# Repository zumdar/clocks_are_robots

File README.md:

# clocks_are_robots
## ECE3872 musical robot team 5B 

Tinkercad Simulation of Arduino and circuity: <br>
https://www.tinkercad.com/things/kZ8lBtSx1vj-copy-of-ece3872-time-zeeper/editel?sharecode=Mxh5uRSaNloz5li4VxAIo-LYPFh9B_5_VCMgjHP5ZlA

**Arduino Pinouts**

A0 - Audio in <br>
A1 - Enveloped audio in<br>
A2 - Octave knob <br>
<br><br>
[D4 - D7] are for stepper motor<br>
D4 - AIn1<br>
D5 - Ain2<br>
D6 - Bin1<br>
D7 - Bin2<br>
D8 - Start/Stop Button<br>
D9 - Tone out <br>
D10 - Servo out<br>
D12 - Neopixel LED out<br>

# glamour shots

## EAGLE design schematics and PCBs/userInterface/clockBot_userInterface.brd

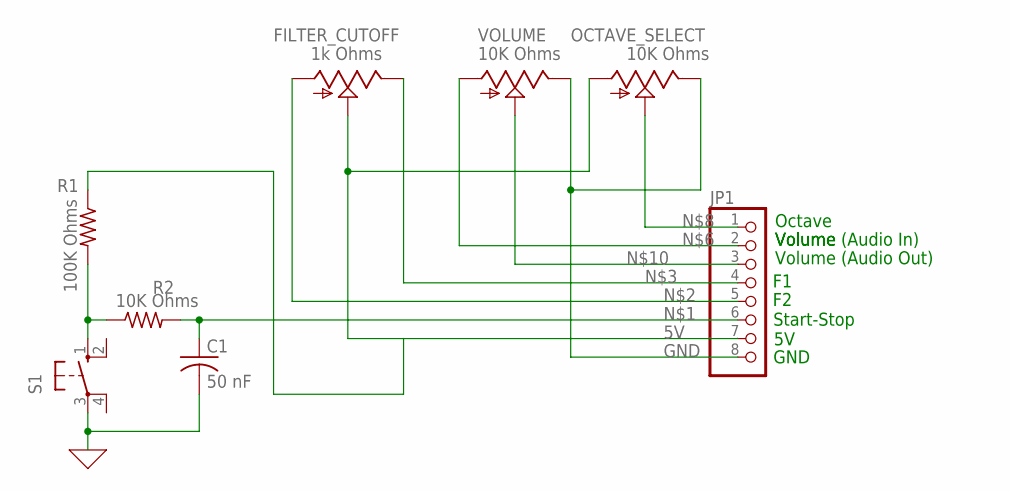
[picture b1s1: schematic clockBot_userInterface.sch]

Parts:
C1: 50 nF; C025-025X050
FILTER_CUTOFF: 1k Ohms; S64W
JP1: PINHD-1X8; 1X08
OCTAVE_SELECT: 10K Ohms; S64W
R1: 100K Ohms; 0204/7
R2: 10K Ohms; 0204/7
S1: 10-XX; B3F-10XX
VOLUME: 10K Ohms; S64W

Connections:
0: C1.2, S1.3
5V: FILTER_CUTOFF.S, JP1.7, OCTAVE_SELECT.A, R1.1
GND: JP1.8, OCTAVE_SELECT.E, VOLUME.E
unnamed: C1.1, JP1.6, R2.2
unnamed: FILTER_CUTOFF.A, JP1.5
unnamed: FILTER_CUTOFF.E, JP1.4
unnamed: JP1.2, VOLUME.A
unnamed: R1.2, R2.1, S1.1 (S)
unnamed: JP1.1, OCTAVE_SELECT.S
unnamed: JP1.3, VOLUME.S

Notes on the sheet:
Octave
Volume
GND
Start-Stop
Volume (Audio Out)
Volume (Audio In)

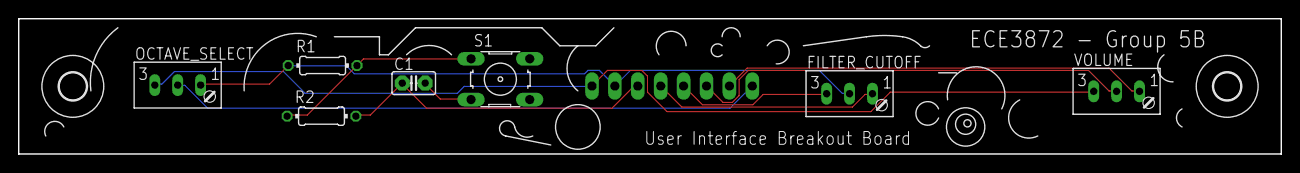
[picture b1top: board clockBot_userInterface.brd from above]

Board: 2 copper layers, 140.0 x 15.0 mm, 10 parts (1 on the bottom side), 10 nets.

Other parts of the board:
U$1, U$2: 3,0

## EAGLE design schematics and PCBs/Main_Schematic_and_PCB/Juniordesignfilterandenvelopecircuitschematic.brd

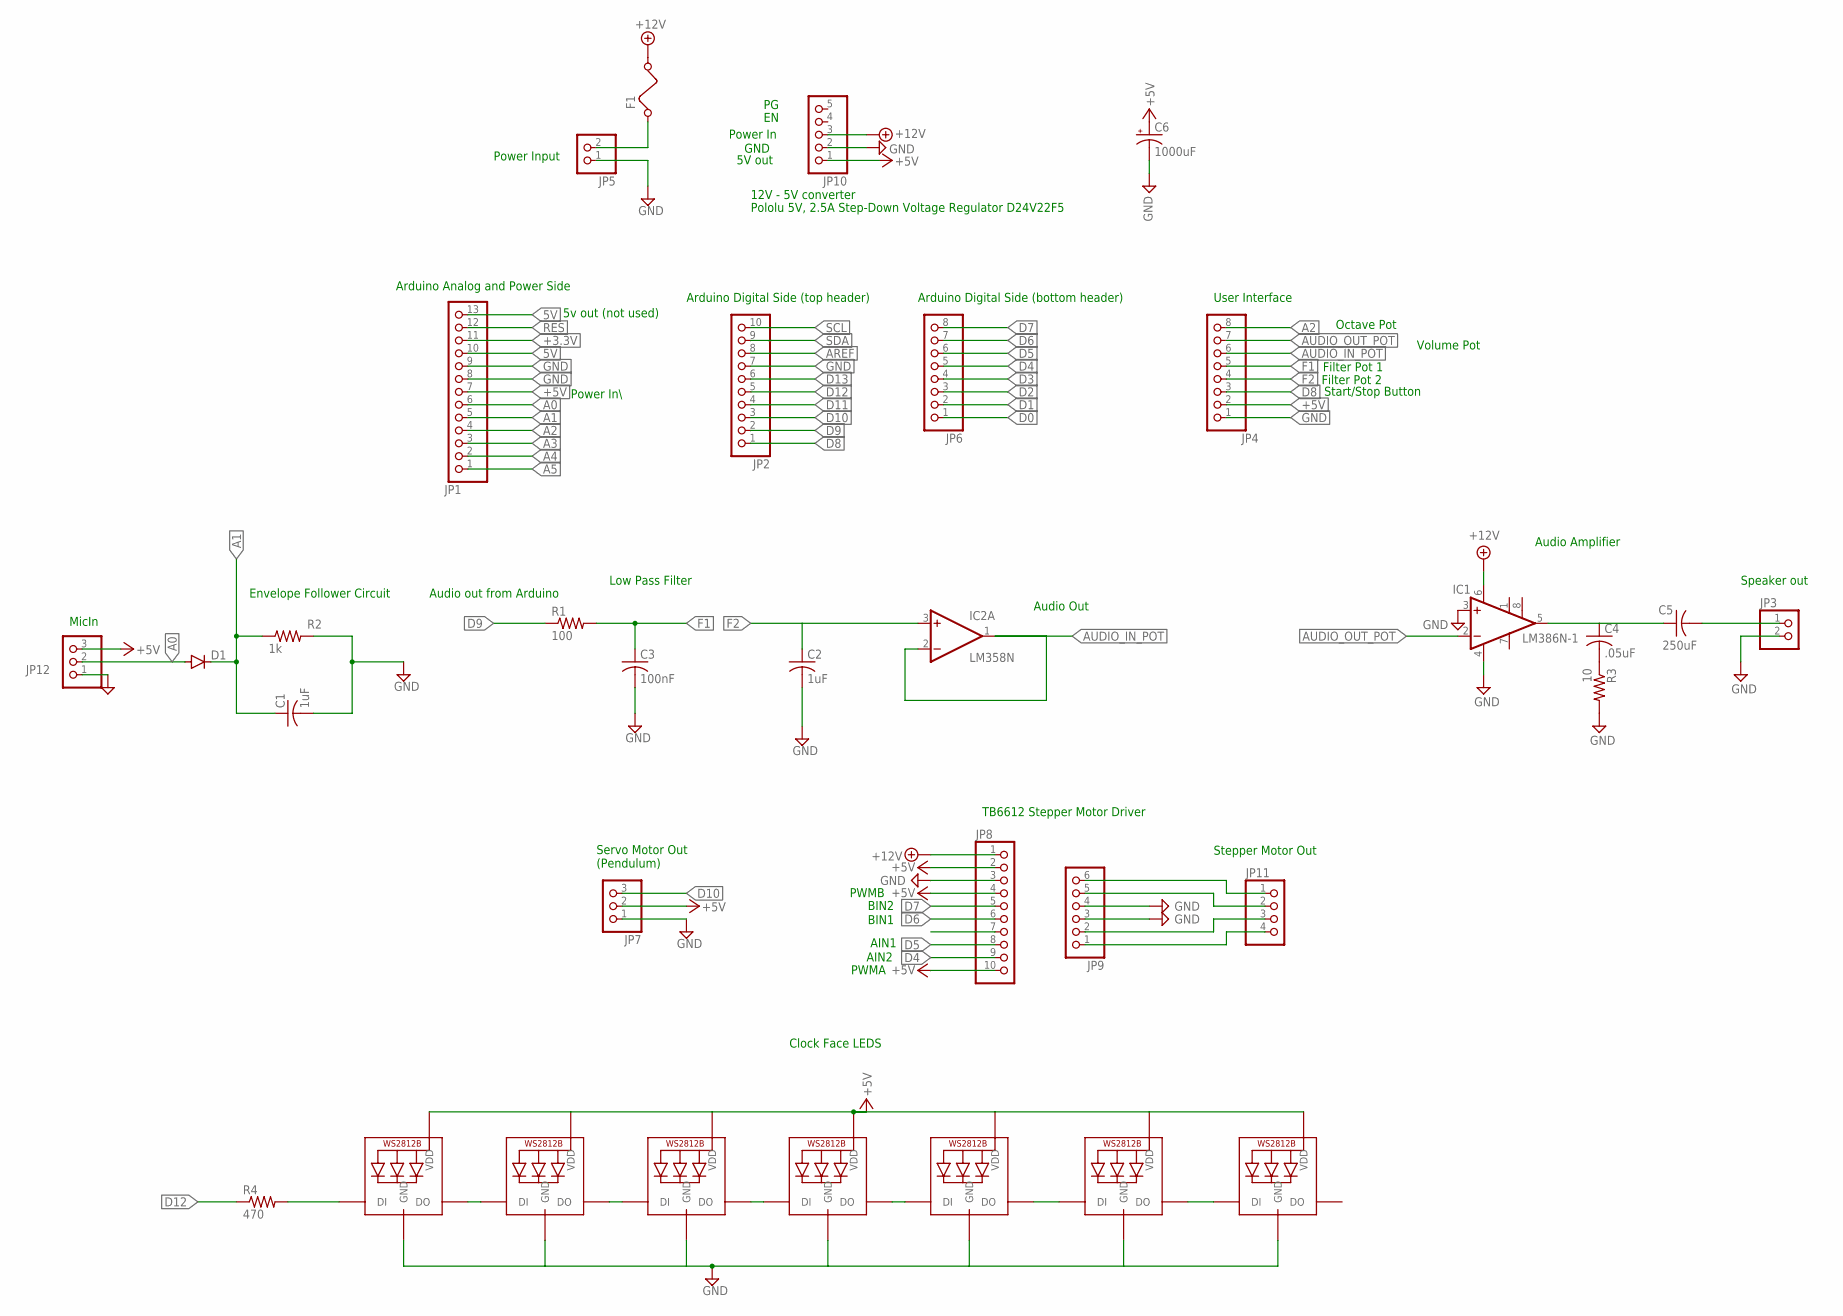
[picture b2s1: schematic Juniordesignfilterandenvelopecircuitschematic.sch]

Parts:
C1: 1uF; C025-050X050
C2: 1uF; C025-040X050
C3: 100nF; C025-040X050
C4: .05uF; C025-040X050
C5: 250uF; C025-040X050
C6: 1000uF; E5-8,5
D1: 1N4148DO35-7; DO35-7
F1: FUSE
IC1: LM386N-1; DIL08
IC2: LM358N; DIL08
JP1: PINHD-1X13; 1X13
JP2, JP8: PINHD-1X10; 1X10
JP3, JP5: PINHD-1X2; 1X02
JP4, JP6: PINHD-1X8; 1X08
JP7, JP12: PINHD-1X3; 1X03
JP9: PINHD-1X6; 1X06
JP10: PINHD-1X5; 1X05
JP11: PINHD-1X4; 1X04
LED2, LED3, LED4, LED5, LED6, LED7, LED8: WS2812B_5050N; WS2812B-NARROW
R1: 100; 0204/7
R2: 1k; 0204/7
R3: 10; 0204/7
R4: 470; 0204/7

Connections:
5V: JP1.10, JP1.13
+3.3V: JP1.11
+5V: C6.+, JP1.7, JP4.2, JP7.2, JP8.2, JP8.4, JP8.10, JP10.1, JP12.3, LED2.1-VDD (VDD), LED3.1-VDD (VDD), LED4.1-VDD (VDD), LED5.1-VDD (VDD), LED6.1-VDD (VDD), LED7.1-VDD (VDD), LED8.1-VDD (VDD)
+12V: F1.2, IC1.6 (VS), JP8.1, JP10.3
A0: D1.A, JP1.6, JP12.2
A1: C1.1, D1.C, JP1.5, R2.1
A2: JP1.4, JP4.8
A3: JP1.3
A4: JP1.2
A5: JP1.1
AREF: JP2.8
AUDIO_IN_POT: IC2.1 (OUT), IC2.2 (-IN), JP4.6
AUDIO_OUT_POT: IC1.2 (-IN), JP4.7
D0: JP6.1
D1: JP6.2
D2: JP6.3
D3: JP6.4
D4: JP6.5, JP8.9
D5: JP6.6, JP8.8
D6: JP6.7, JP8.6
D7: JP6.8, JP8.5
D8: JP2.1, JP4.3
D9: JP2.2, R1.1
D10: JP2.3, JP7.3
D11: JP2.4
D12: JP2.5, R4.1
D13: JP2.6
F1: C3.1, JP4.5, R1.2
F2: C2.1, IC2.3 (+IN), JP4.4
GND: C1.2, C2.2, C3.2, C6.-, IC1.3 (+IN), IC1.4 (GND), JP1.8, JP1.9, JP2.7, JP3.2, JP4.1, JP5.1, JP7.1, JP8.3, JP9.3, JP9.4, JP10.2, JP12.1, LED2.3-GND (GND), LED3.3-GND (GND), LED4.3-GND (GND), LED5.3-GND (GND), LED6.3-GND (GND), LED7.3-GND (GND), LED8.3-GND (GND), R2.2, R3.2
unnamed: C4.2, R3.1
unnamed: F1.1, JP5.2
unnamed: LED2.4-DIN (DI), R4.2
unnamed: C4.1, C5.1, IC1.5 (OUT)
unnamed: C5.2, JP3.1
unnamed: LED2.2-DOUT (DO), LED3.4-DIN (DI)
unnamed: LED4.2-DOUT (DO), LED5.4-DIN (DI)
unnamed: LED5.2-DOUT (DO), LED6.4-DIN (DI)
unnamed: LED6.2-DOUT (DO), LED7.4-DIN (DI)
unnamed: LED7.2-DOUT (DO), LED8.4-DIN (DI)
unnamed: LED3.2-DOUT (DO), LED4.4-DIN (DI)
unnamed: JP9.6, JP11.1
unnamed: JP9.5, JP11.2
unnamed: JP9.2, JP11.3
unnamed: JP9.1, JP11.4
RES: JP1.12
SCL: JP2.10
SDA: JP2.9
V+: IC2.8 (V+)
V-: IC2.4 (V-)

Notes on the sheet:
Envelope Follower Circuit
MicIn
Audio Out
Power Input
Low Pass Filter
Power In
GND
5V out
12V - 5V converter
Pololu 5V, 2.5A Step-Down Voltage Regulator D24V22F5
Power In\
5v out (not used)
Arduino Analog and Power Side
Octave Pot
Volume Pot
Filter Pot 1
Filter Pot 2
Start/Stop Button
Speaker out
User Interface
Servo Motor Out (Pendulum)
Clock Face LEDS
Arduino Digital Side (bottom header)
Arduino Digital Side (top header)
PWMA
PWMB
AIN1
AIN2
BIN1
BIN2
TB6612 Stepper Motor Driver
Stepper Motor Out
Audio out from Arduino
Audio Amplifier

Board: 2 copper layers, 38 parts (16 on the bottom side), 34 nets, no tracks yet.

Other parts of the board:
U$1: 5,5
U$2, U$3, U$4, U$5: 3,0

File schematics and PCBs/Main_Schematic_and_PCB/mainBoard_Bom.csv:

"Qty";"Value";"Device";"Package";"Parts";"Description";"";
"2";"";"PINHD-1X10";"1X10";"JP2, JP8";"PIN HEADER";"";
"1";"";"PINHD-1X13";"1X13";"JP1";"PIN HEADER";"";
"2";"";"PINHD-1X2";"1X02";"JP3, JP5";"PIN HEADER";"";
"2";"";"PINHD-1X3";"1X03";"JP7, JP12";"PIN HEADER";"";
"1";"";"PINHD-1X4";"1X04";"JP11";"PIN HEADER";"";
"1";"";"PINHD-1X5";"1X05";"JP10";"PIN HEADER";"";
"1";"";"PINHD-1X6";"1X06";"JP9";"PIN HEADER";"";
"2";"";"PINHD-1X8";"1X08";"JP4, JP6";"PIN HEADER";"";
"1";".05uF";"C-US025-040X050";"C025-040X050";"C4";"CAPACITOR, American symbol";"";
"1";"10";"R-US_0204/7";"0204/7";"R3";"RESISTOR, American symbol";"";
"1";"100";"R-US_0204/7";"0204/7";"R1";"RESISTOR, American symbol";"";
"1";"1000uF";"CPOL-USE5-8.5";"E5-8,5";"C6";"POLARIZED CAPACITOR, American symbol";"";
"1";"100nF";"C-US025-040X050";"C025-040X050";"C3";"CAPACITOR, American symbol";"";
"1";"1N4148DO35-7";"1N4148DO35-7";"DO35-7";"D1";"DIODE";"";
"1";"1k";"R-US_0204/7";"0204/7";"R2";"RESISTOR, American symbol";"";
"1";"1uF";"C-US025-040X050";"C025-040X050";"C2";"CAPACITOR, American symbol";"";
"1";"1uF";"C-US025-050X050";"C025-050X050";"C1";"CAPACITOR, American symbol";"";
"1";"250uF";"C-US025-040X050";"C025-040X050";"C5";"CAPACITOR, American symbol";"";
"1";"470";"R-US_0204/7";"0204/7";"R4";"RESISTOR, American symbol";"";
"1";"LM358N";"LM358N";"DIL08";"IC2";"OP AMP also LM158; LM258; LM2904";"";
"1";"LM386N-1";"LM386N-1";"DIL08";"IC1";"Low Voltage Audio Power Amplifier";"";
"7";"WS2812B_5050N";"WS2812B_5050N";"WS2812B-NARROW";"LED2, LED3, LED4, LED5, LED6, LED7, LED8";"";"";

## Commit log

2021-02-05 adding arduino files
2021-02-08 Initial matlab setup
2021-02-10 Low Pass Filter
2021-02-15 Envelope detector minus env_freq_axis_kHz
2021-02-16 arduino testing code
2021-02-17 Tempo detect draft, modified env detect
2021-02-17 Re-including changes to visualization code
2021-02-18 adding preliminary output filter + EG schematic
2021-02-18 updated the arduino code. now the servos rotate with the notes and the leds light up with the notes. also the metronome servo works too
2021-02-18 updated the tinkercad file link
2021-02-19 Requantize is independent. Fixed tempo_detection bug with silent start of signal
2021-02-19 Sync_time draft
2021-02-25 Working (but dense) sync_time
2021-03-01 adding clock face 3d file
2021-03-02 ece3872_clockBot_arduino_2
2021-03-05 Stepper Motor
2021-03-05 Updates after test
2021-03-05 Stepper motor update
2021-03-05 Stepper Motor updated
2021-03-05 changed stepper motor code to work with 1.8 degree motor
2021-03-09 clockbot user interface
2021-03-09 rearranged schematic and pcb folders to be easier to navigate
2021-03-09 Interface update
2021-03-10 organized folders and added erin grace schematic
2021-03-10 User interface update
2021-03-10 Updated user interface
2021-03-11 main board schematic done
2021-03-11 fixing formatting on readme.md
2021-03-11 8pin molex user interface
2021-03-11 PCB Board
2021-03-12 User interface PCB update
2021-03-12 Fixed switch on user interface
2021-03-12 User itnerface switch update
2021-03-12 clockface svg file for laser cut
2021-03-12 main board pcb initial layout
2021-03-12 updated main pcb
2021-03-12 User interface single row molex
2021-03-12 changed header for userinterface
2021-03-12 User interface labels
2021-03-13 Finalized board
    Changed labels and performed a design rule check.
2021-03-13 finalized PCBs and exported gerbers
2021-03-13 adding some images
2021-03-16 Drafted diagnosis mode (processing code may block)
2021-03-16 Small fixes (syntax errors & var definitions)
2021-03-19 updated new clock face with the finalized pcb
2021-03-19 changed readme again
2021-03-26 Working tempo detection
2021-03-26 simultaneously generate & process audio signal
2021-03-29 Test mode
2021-03-29 Test mode fix 2
2021-03-31 Partially Verified Delay Sync
2021-03-31 Small tempo-sampling fix
2021-03-31 Reintigrating processing code w/ button press
2021-03-31 Removed nonessential loops, conventional edits
2021-04-02 Remove code from processing test
2021-04-02 Test Mode debugged
2021-04-02 laser cut svg files added
2021-04-02 Added LEDs for play/test and octave select
2021-04-02 LED test/play fix
2021-04-05 changed penduluum code and threw in simple conductor code
2021-04-05 Add Input Test
2021-04-05 Including Manual Mode
2021-04-06 lab work
2021-04-07 updating svgs
2021-04-07 Stepper motor integrated into Main code
2021-04-07 Added Stepper motor to octave select and test mode
2021-04-07 Extra closing bracket ruined everything
2021-04-09 Processing Test - tempo w/ mic
2021-04-09 Including fresh tempo code w/ main
2021-04-09 Removing Delay and Print statements
2021-04-09 Fix for metronome code
2021-04-09 updated svgs
2021-04-09 Fix octave
2021-04-09 Fixed input test LEDS
2021-04-09 steper changes
2021-04-09 Fixed strip show
2021-04-09 Stepper motor auto change after octave select
2021-04-09 metronome code
2021-04-09 Slow down input test
2021-04-09 Stepper motor auto change after octave select (2)
2021-04-09 William's Stuff
2021-04-09 Metronome
2021-04-09 Stepper Motor Stuff
2021-04-11 clock face
